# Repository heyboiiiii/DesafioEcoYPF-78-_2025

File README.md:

# PROYECTO YPF

## El proyecto original tenía como objetivo desarrollar la Computadora del Auto completa para el Desafío ECO YPF, incorporando diversos módulos de control y adquisición de datos para asistir al piloto. Dentro del conjunto de la Computadora, el Sistema de Control de Velocidad Crucero representaba solo una de las funcionalidades planificadas.
Sin embargo, durante el proceso surgieron diversos imprevistos que modificaron el alcance del proyecto. El viaje al autódromo, condiciones climáticas de tormenta que impidieron trabajar sobre el vehículo y, finalmente, un choque que dañó la placa principal del auto, imposibilitaron continuar con la integración de la computadora completa. Como consecuencia, se decidió enfocar el proyecto al desarrollo y funcionamiento del sistema de velocidad crucero utilizando una placa experimental.
Esta reestructuración permitió concentrarse en el diseño, programación y prueba del sistema decontrol de velocidad mediante ESP32, GPS y servomotor, con un sistema PID. Aunque no fue posible implementar la computadora entera del vehículo, el repositorio oficial del proyecto incluye el código completo de todos los módulos de la computadora, documentado y accesible.
En este informe se detalla el funcionamiento del sistema de velocidad crucero, su implementación, las pruebas realizadas y los resultados obtenidos en función del ensayo con la placa experimental.

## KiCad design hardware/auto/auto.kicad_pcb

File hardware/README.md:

YPF KICAD DESIGNS

Esquemas y PCB de KICAD para la computadora del auto del "Desafío ECO YPF" y sus submódulos.

Proyecto *AUTO*:
    
    Computadora basada en un ESP32, una pantalla led ILI9844 montada en el volante(SPI), un acelerometro(MPU6050), modulo GPS(NEO6M) y un modulo LORA(XL1278).  

Proyecto *SHIELD_LORA*:
    
    Adaptación del módulo SMT1278 LoRa a un conector de 5 pines (header de 2.54 mm).

Proyecto *ACS_V_placa*:
    
    Aquí es donde los terminales de las baterías se conectan al sensor de corriente ACS712 (30A) y al divisor de voltaje.

    Esta placa se conectará a la placa del Proyecto AUTO mediante 3 cables.

Project_libraries: librerias de simbolos y huellas de los componentes creados para adaptar cada modulo a la placa.

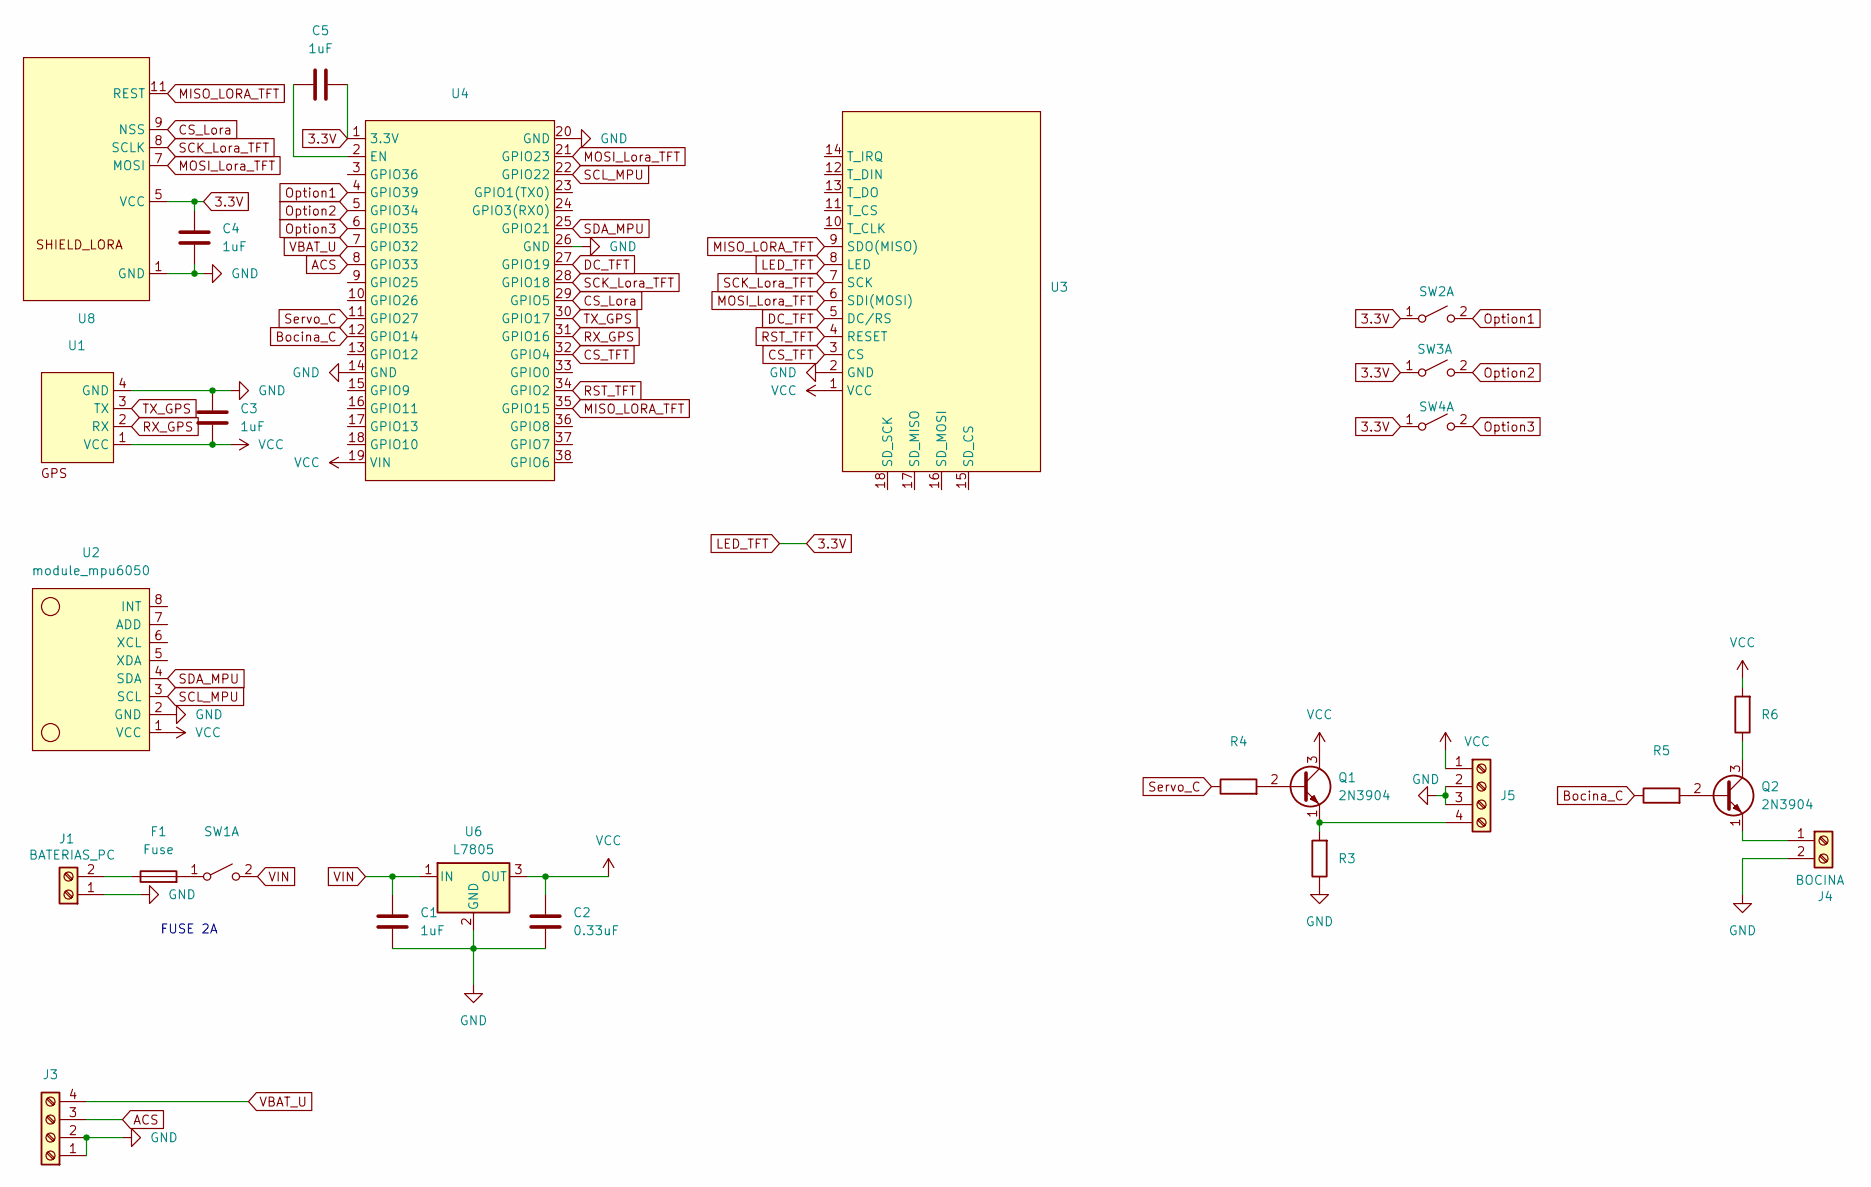
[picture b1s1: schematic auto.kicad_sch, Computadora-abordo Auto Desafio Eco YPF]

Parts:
C1, C4, C5: 1uF; R_Axial_DIN0204_L3.6mm_D1.6mm_P5.08mm_Horizontal
C2: 0.33uF; R_Axial_DIN0204_L3.6mm_D1.6mm_P5.08mm_Horizontal
C3: 1uF; R_Axial_DIN0204_L3.6mm_D1.6mm_P7.62mm_Horizontal
F1: Fuse; Fuseholder_Clip-5x20mm_Littelfuse_445-030_Inline_P20.50x5.2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
J1: BATERIAS_PC; Molex_KK-396_5273-02A_1x02_P3.96mm_Vertical
J3: Screw_Terminal_01x04; Molex_KK-396_5273-04A_1x04_P3.96mm_Vertical
J4: BOCINA; R_Axial_DIN0204_L3.6mm_D1.6mm_P5.08mm_Horizontal
J5: Screw_Terminal_01x04; PinSocket_1x04_P2.54mm_Vertical
Q1, Q2: 2N3904; TO-92_Inline
R3, R5, R6: 10k; R_Axial_DIN0204_L3.6mm_D1.6mm_P5.08mm_Horizontal
R4: 10k; R_Axial_DIN0207_L6.3mm_D2.5mm_P10.16mm_Horizontal
SW1: SW_DPST_x2; SW_DIP_SPSTx01_Slide_9.78x4.72mm_W7.62mm_P2.54mm
SW2: SW1; SW_PUSH-12mm_Wuerth-430476085716
SW3, SW4: SW_DPST_x2; SW_PUSH-12mm_Wuerth-430476085716
U1: GY-NEO6MV2
U2: module_mpu6050; module_MPU6050
U3: tft_3.5_display
U4: esp32
U6: L7805; TO-220-3_Vertical
U8: SHIELD XL1278

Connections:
3.3V: C4.1, C5.2, SW2.1 (A), SW3.1 (A), SW4.1 (A), U3.8 (LED), U4.1 (3.3V), U8.5 (VCC)
ACS: J3.3, U4.8 (GPIO33)
Bocina_C: R5.1, U4.12 (GPIO14)
CS_Lora: U4.29 (GPIO5), U8.9 (NSS)
CS_TFT: U3.3 (CS), U4.32 (GPIO4)
DC_TFT: U3.5 (DC/RS), U4.27 (GPIO19)
GND: C1.2, C2.2, C3.1, C4.2, J1.1, J3.1, J3.2, J4.2, J5.2, J5.3, R3.1, U1.4 (GND), U2.2 (GND), U3.2 (GND), U4.14 (GND), U4.20 (GND), U4.26 (GND), U6.2 (GND), U8.1 (GND)
MISO_LORA_TFT: U3.9 (SDO(MISO)), U4.35 (GPIO15), U8.11 (REST)
MOSI_Lora_TFT: U3.6 (SDI(MOSI)), U4.21 (GPIO23), U8.7 (MOSI)
unnamed: F1.1, J1.2
unnamed: J4.1, Q2.1 (E)
unnamed: J5.4, Q1.1 (E), R3.2
unnamed: Q1.2 (B), R4.2
unnamed: Q2.2 (B), R5.2
unnamed: Q2.3 (C), R6.1
unnamed: F1.2, SW1.1 (A)
unnamed: C5.1, U4.2 (EN)
Option1: SW2.2 (B), U4.4 (GPIO39)
Option2: SW3.2 (B), U4.5 (GPIO34)
Option3: SW4.2 (B), U4.6 (GPIO35)
RST_TFT: U3.4 (RESET), U4.34 (GPIO2)
RX_GPS: U1.2 (RX), U4.31 (GPIO16)
SCK_Lora_TFT: U3.7 (SCK), U4.28 (GPIO18), U8.8 (SCLK)
SCL_MPU: U2.3 (SCL), U4.22 (GPIO22)
SDA_MPU: U2.4 (SDA), U4.25 (GPIO21)
Servo_C: R4.1, U4.11 (GPIO27)
TX_GPS: U1.3 (TX), U4.30 (GPIO17)
VBAT_U: J3.4, U4.7 (GPIO32)
VCC: C2.1, C3.2, J5.1, Q1.3 (C), R6.2, U1.1 (VCC), U2.1 (VCC), U3.1 (VCC), U4.19 (VIN), U6.3 (OUT)
VIN: C1.1, SW1.2 (B), U6.1 (IN)

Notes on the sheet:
FUSE 2A

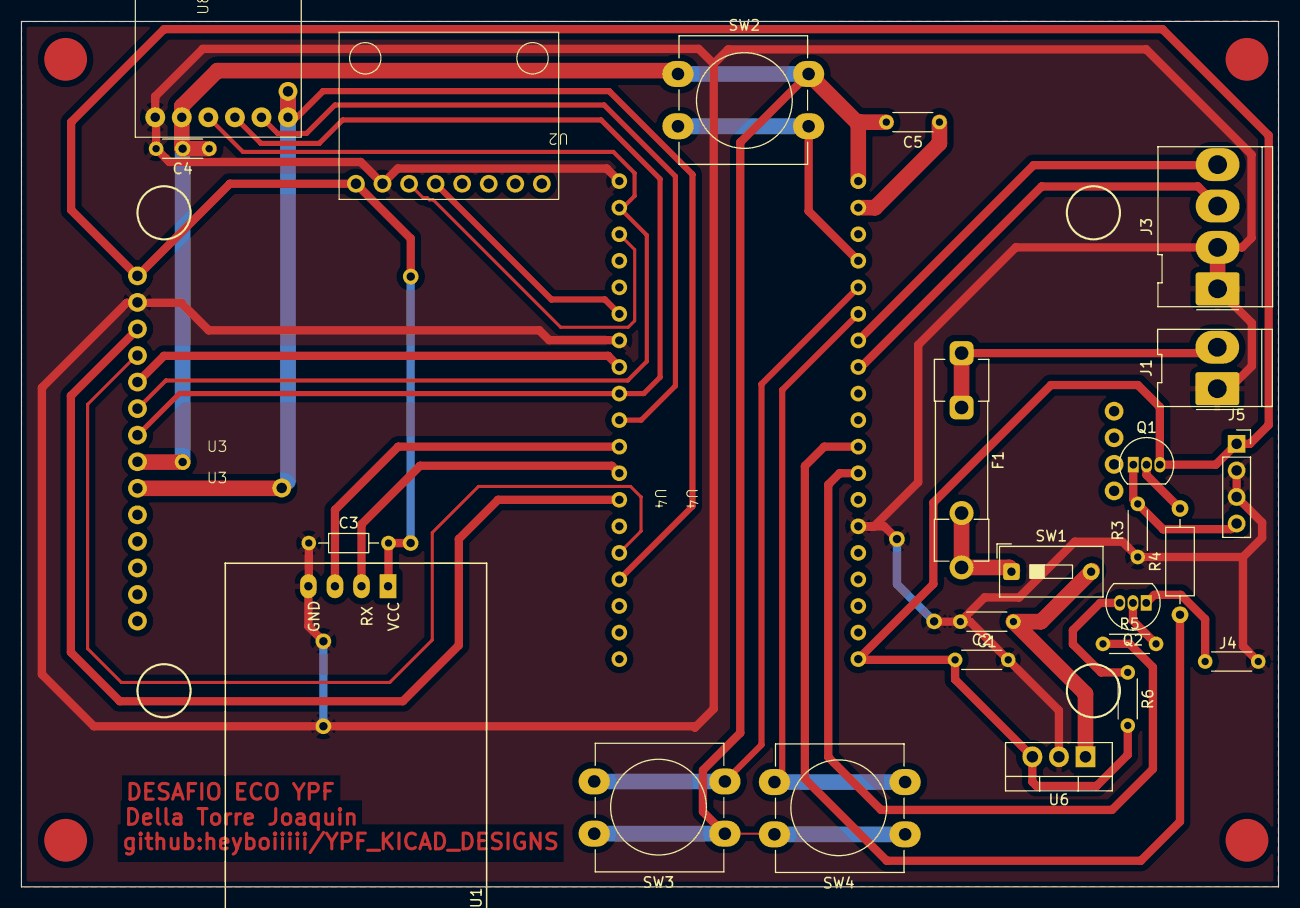
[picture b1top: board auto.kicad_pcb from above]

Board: 2 copper layers, 120.2 x 82.8 mm, 26 parts (0 on the bottom side), 30 nets.

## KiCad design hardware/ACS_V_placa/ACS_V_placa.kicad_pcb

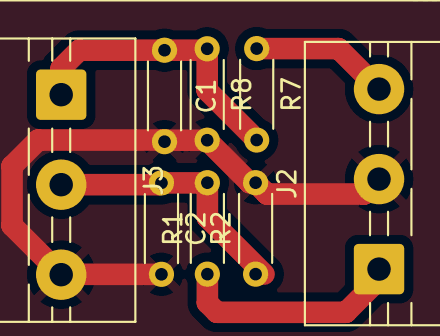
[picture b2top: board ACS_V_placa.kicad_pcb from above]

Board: 2 copper layers, 8 parts (0 on the bottom side), 5 nets.

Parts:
C1, C2: C; R_Axial_DIN0204_L3.6mm_D1.6mm_P5.08mm_Horizontal
J2: BATERIA_AUTO; TerminalBlock_MaiXu_MX126-5.0-03P_1x03_P5.00mm
J3: Cableado_hacia_auto; TerminalBlock_MaiXu_MX126-5.0-03P_1x03_P5.00mm
R1: 10K; R_Axial_DIN0204_L3.6mm_D1.6mm_P5.08mm_Horizontal
R2: 10k; R_Axial_DIN0204_L3.6mm_D1.6mm_P5.08mm_Horizontal
R7: 220k; R_Axial_DIN0204_L3.6mm_D1.6mm_P5.08mm_Horizontal
R8: 4.7k; R_Axial_DIN0204_L3.6mm_D1.6mm_P5.08mm_Horizontal

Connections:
GND: C1.2, C2.2, J2.2, J3.3, R2.2, R8.2
IBAT_U: C2.1, J3.2, R1.2, R2.1
VBAT+: J2.3, R7.1
VBAT_OUT: J2.1, R1.1
VBAT_U: C1.1, J3.1, R7.2, R8.1

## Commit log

2025-11-27 Se subieron toda la info utilizada y programa desarrollo para la realizacion del proyecto YPF 2025: AUTO 78.
2025-11-27 add image
2025-11-27 se agregaron informes IEEE
2025-11-27 se agreraron images del auto
